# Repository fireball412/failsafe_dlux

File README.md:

# failsafe_dlux
 Failsafe for Turnigy dlux 250A HV 14s 60v ESC

Issue: The ESC has a hold time of almost 3 seconds in case of PPM signal loss. The PPM signal loss may occur if RX power supply fails (or in case of reception issues without RX-failsafe).

Solution approach: The circuit is powered by the RX. The supply is decoupled by a schottky diode and buffered by a capacitor. In case of RX power failure the circuit sets the ESC to the predefined failsafe position (failsafe_pos). Power failure is detected by comparing the supply in front of the diode with the predefined limit (voltagelimit). 
Failsafe is also triggered if the last proper PPM signal is older than the predefined limit (delaylimit).

red LED: indicates if output signal is below or equal failsafe position (either due to corresponding input signal or activated failsafe)
Blink code: 1 blink = PPM signal loss occurred at least once, 2 blínks = supply voltage was below limit at least once

demonstration:
https://www.youtube.com/watch?v=K2Zalw2rsIU

old version history

V.0.9: 
- first try

V.1.0: 
- first stable version
- improved software structure
- blink code for errors
- solution for delay control that was challenged by interrupt 

V.1.0.1:
- adapted for nano_RC_hold_V1.0 PCBs (pin number for input and output); no change needed for nano_RC_hold_V1.1 PCBs

V.1.0.2:
- using map function to scale ADC voltage to input voltage
- implementation 10k/68k voltage divider for 8.4V input voltage
- implementation of pistole grip stick conversion (pistol grip transmitter rest in neutral position, many ESC require -100% signal to stop)

2020/12/18 moved to github

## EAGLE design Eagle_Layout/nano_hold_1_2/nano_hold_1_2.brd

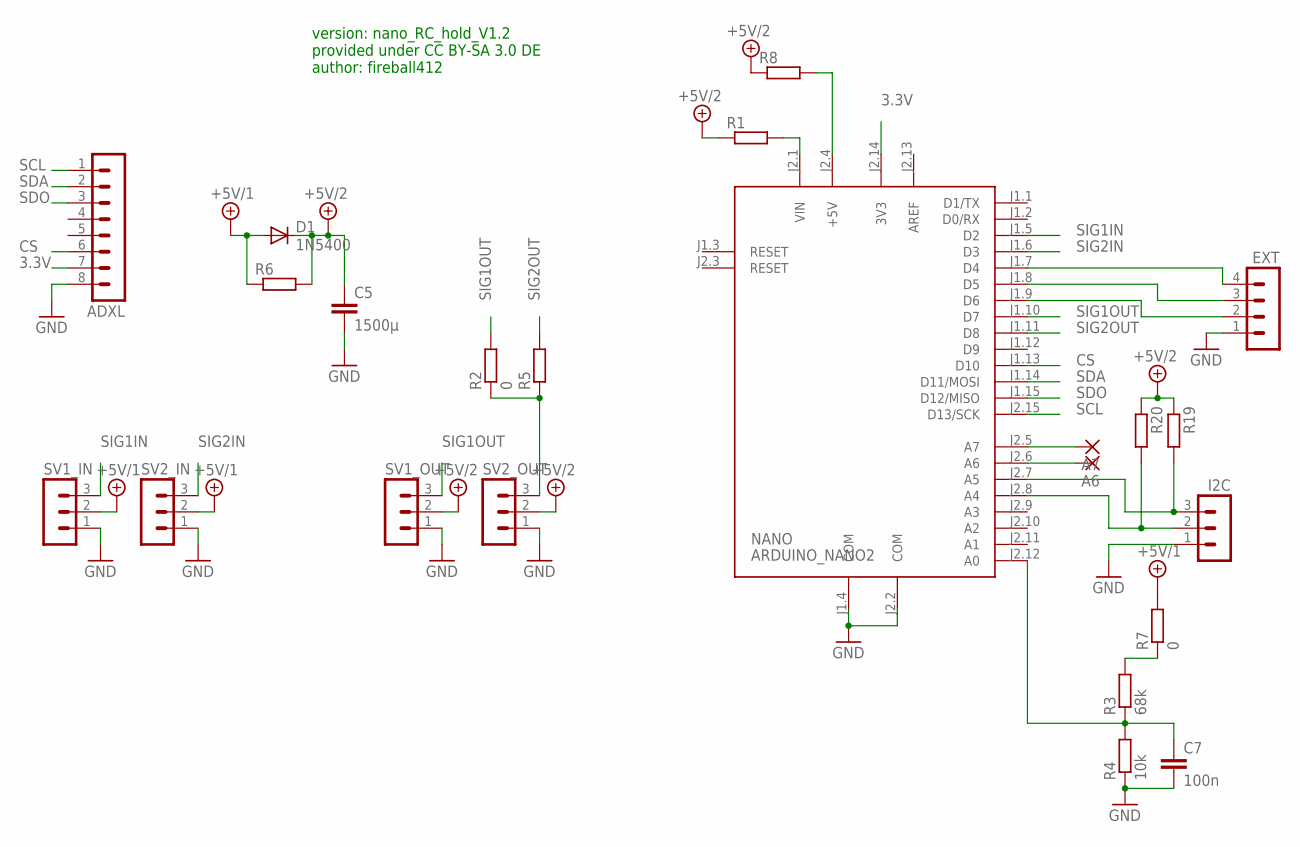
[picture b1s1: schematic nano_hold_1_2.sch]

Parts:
A6, A7: WIREPAD2,15/1,0; 2,15/1,0
ADXL: MA08-1
C5: 1500µ; C050H075X075
C7: 100n; C0805
D1: 1N5400; DO201-15
EXT: MA04-1
I2C: MA03-1
NANO: ARDUINO_NANO2
R1, R5, R6, R8, R19, R20: R-EU_R0805; R0805
R2, R7: 0; R0805
R3: 68k; R0805
R4: 10k; R0805
SV1_IN, SV1_OUT, SV2_IN, SV2_OUT: MA03-1

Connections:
3.3V: ADXL.7, NANO.J2.14 (3V3)
+5V/1: D1.A, R6.1, R7.2, SV1_IN.2, SV2_IN.2
+5V/2: C5.1, D1.C, R1.1, R6.2, R8.1, R19.1, R20.1, SV1_OUT.2, SV2_OUT.2
AREF: NANO.J2.13 (AREF)
CS: ADXL.6, NANO.J1.13 (D10)
GND: ADXL.8, C5.2, C7.2, EXT.1, I2C.1, NANO.J1.4 (COM), NANO.J2.2 (COM), R4.1, SV1_IN.1, SV1_OUT.1, SV2_IN.1, SV2_OUT.1
unnamed: NANO.J2.1 (VIN), R1.2
unnamed: C7.1, NANO.J2.12 (A0), R3.1, R4.2
unnamed: R2.1, R5.1, SV2_OUT.3
unnamed: EXT.4, NANO.J1.7 (D4)
unnamed: EXT.3, NANO.J1.8 (D5)
unnamed: NANO.J2.4 (+5V), R8.2
unnamed: EXT.2, NANO.J1.9 (D6)
unnamed: R3.2, R7.1
unnamed: A7.1, NANO.J2.5 (A7)
unnamed: A6.1, NANO.J2.6 (A6)
unnamed: I2C.3, NANO.J2.7 (A5), R19.2
unnamed: I2C.2, NANO.J2.8 (A4), R20.2
SCL: ADXL.1, NANO.J2.15 (D13/SCK)
SDA: ADXL.2, NANO.J1.14 (D11/MOSI)
SDO: ADXL.3, NANO.J1.15 (D12/MISO)
SIG1IN: NANO.J1.5 (D2), SV1_IN.3
SIG1OUT: NANO.J1.10 (D7), R2.2, SV1_OUT.3
SIG2IN: NANO.J1.6 (D3), SV2_IN.3
SIG2OUT: NANO.J1.11 (D8), R5.2

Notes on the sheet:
version: nano_RC_hold_V1.2 provided under CC BY-SA 3.0 DE author: fireball412

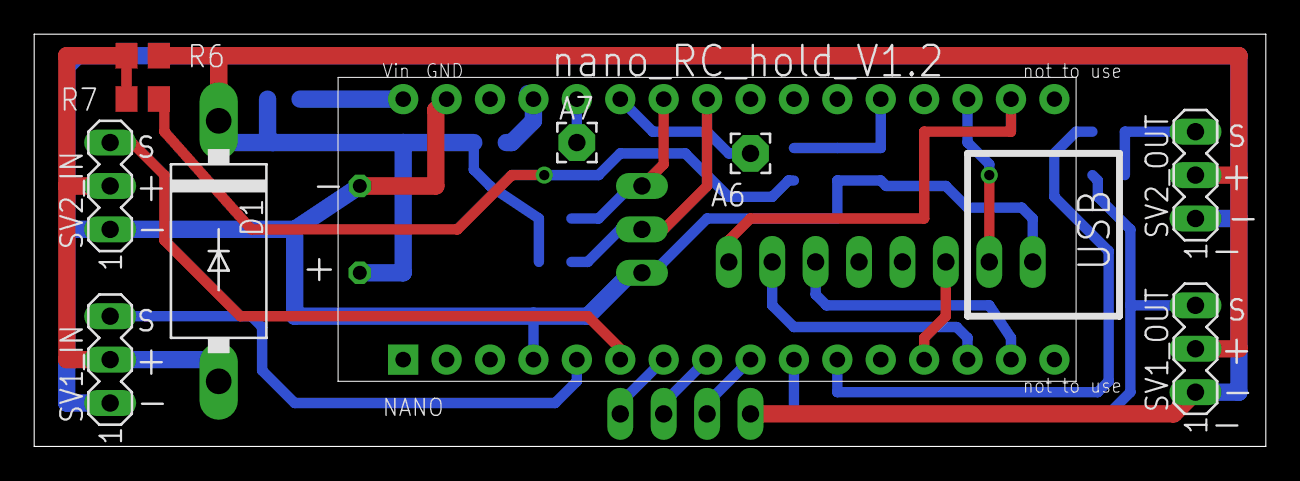
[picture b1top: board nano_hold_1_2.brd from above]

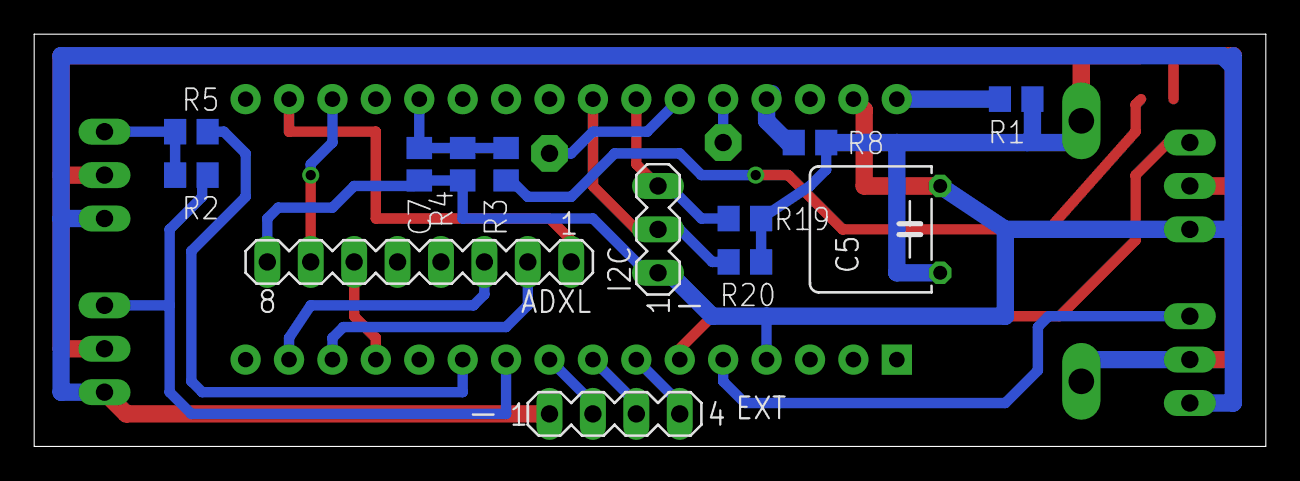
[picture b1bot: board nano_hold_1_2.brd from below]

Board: 2 copper layers, 72.1 x 24.1 mm, 23 parts (13 on the bottom side), 24 nets.

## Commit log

2020-12-18 Create arduino_nano_firmware.ino
    append Arduino project
2020-12-18 adding files
    layout, ,manual, ...
2020-12-27 Update arduino_nano_firmware.ino
    Some really important change :-)
2020-12-27 Update arduino_nano_firmware.ino
    redo change
